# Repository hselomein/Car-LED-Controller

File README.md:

# Car-LED-Controller

Credits:
  - Corey Davis created the project and put together the prototypes.
  - Yves Avady wrote the code for this project.

This project controls an addressable LED Strip and LED matrix using the light inputs from a car electrical system.

With this project, we are taking an esp32 microcontroller and making an LED controller for the strip. 
The LED strip is a 12v WS2811 with 120 LEDs per meter

LED Strip Actions:
- Startup is a night rider style sweep 3 times until it is a solid white bar
- DRL Modes will control the LED strip brightness.

-  When DRLs are in Daytime Running Light Mode strip will be at full brightness
-  When DRLs are used as parking lights, the strip will be dimmed to a lower brightness
  
- Horn usage makes the lights turn dark amber to represent "Angry Mode"
- Indicators will show using a single chasing pattern that stays on for as long as the voltage is applied. This is to match the blink of the indicator circuit
- When hazard lights are on there will be a chasing pattern starting from the middle and ending at the ends
- There will be a button to cycle between Normal, Uber, and Lyft Modes
- Uber Mode, the led strip will be a Seafoam Greem color
- LYFT Mode, the led strip will be Magenta
There will be a physical switch installed to disable the light for law enforcement and/or vehicle inspection purposes

There are 5 voltage reading inputs 

  - DRL Left Sensing, 
  - DRL right Sensing,
  - Horn Sensing,
  - Left Indicator,
  - Right Indicator

At powerup LED strip will sweep 3 times each pass leaving the light on brighter until filled.
It'll stay filled white unless another mode is selected or an action happens

2 LED Matrices will be attached to the front and back of the vehicle and show 1 of 3 screens
  - Off or Blank for normal driving mode
  - Uber Mode: Shows Uber logo
  - Lyft Mode: Shows Lyft Logo

Actions:
DRL is in DRL Mode light will be at full brightness
DRL is in parking light mode and will be at half-brightness
When not in Uber or Lyft mode, the LED Matrix will be blank or off
Horn is pressed LED Strip will turn orange for the duration of the press
UBER Mode will turn the lights Cyan and the LED Matrix will show the Uber logo
Lyft Mide will turn the lights Magenta and the LED Matrix will show the Lyft Logo
Angry Mode will be some orangy red color, cant be RED as that is illegal in the front
The left indicator will show a chasing pattern, starting in the center and moving to the left side of the strip
The right indicator will show a chasing pattern, starting in the center and moving to the right side of the strip
Vehicle inspection mode, which will disable the lights, physical switch

There is a parts list so you can build this as well.

How to use with Platform-io IDE:
- You will need the Platformio-ide extension installed in VSCODE to compile the code
The src folder is where the code you want to compile and upload code to the ESP32
The main program code is in the file "main.cpp".

How to use with Arduino IDE
- The Arduino project files are located in the ArduinoIDE folder. This part is not complete still porting the code

This program is modular. You can enable or disable specific features by setting directives to true or false.

Build Configuration Options - This program is modular in the sense that you can have everything (LED Strip, LED Matrix) work or just cartain parts.  
See the Build Configuration Options to enable or disable certain features.

Examples:  
//Build Configuration Options  
  #define DEBUG false       //Enable serial output for debug, change to "false" to disable  
  #define SCREENTEST false  //To enable the boot up screen test, change to "true", to disable change to "false"  
  #define LED_MATRIX true   //Set to "true" if you want to use a 64x64 LED Matrix, "false" to disable  
  #define LED_STRIP true    //Set to "true" if you want to use the led strip, "false" to disable  
  #define NUM_MODES 2       //How many modes will the mode button handle (2 for Uber and Lyft signs)  

Code Notes:
- Car_LED_Controller-LED_Matrix_64x64.ino - this is the program for the 64x64 P2 LED Matrix for the Arduino ide, this still needs to be completed
- Part List - this is the shopping list of parts for this project

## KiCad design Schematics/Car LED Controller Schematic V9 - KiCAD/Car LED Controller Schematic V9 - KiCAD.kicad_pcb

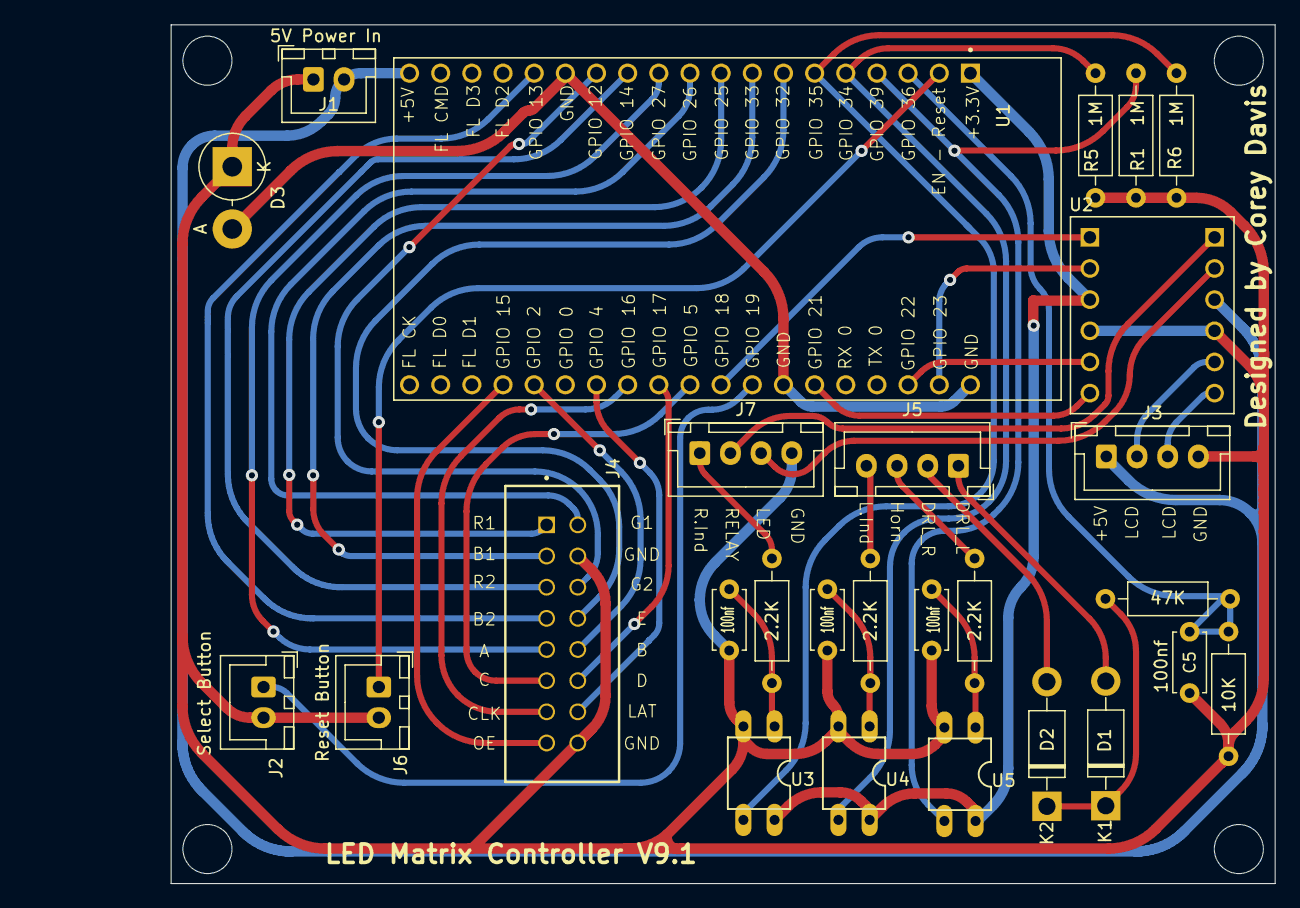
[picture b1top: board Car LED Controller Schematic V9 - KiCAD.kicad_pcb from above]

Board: 2 copper layers, 101.9 x 70.0 mm, 27 parts (0 on the bottom side), 41 nets.

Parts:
C1, C2, C3, C5: 100nf; C_Disc_D4.7mm_W2.5mm_P5.00mm
D1, D2: 1N4007; D_DO-41_SOD81_P10.16mm_Horizontal
D3: D_Schottky; D_DO-201AD_P5.08mm_Vertical_AnodeUp
J1: 5V Power In; JST_XH_B2B-XH-A_1x02_P2.50mm_Vertical
J2: Select Button; JST_XH_B2B-XH-A_1x02_P2.50mm_Vertical
J3: LCD Display; JST_XH_B4B-XH-A_1x04_P2.50mm_Vertical
J4: ZSS-108-01-F-D-506; SAMTEC_ZSS-108-01-F-D-506
J5: DRL, Horn, Indicator; JST_XH_B4B-XH-A_1x04_P2.50mm_Vertical
J6: Reset Button; JST_XH_B2B-XH-A_1x02_P2.50mm_Vertical
J7: DRL, Horn Sense; JST_XH_B4B-XH-A_1x04_P2.50mm_Vertical
R1, R5, R6: 1M; R_Axial_DIN0207_L6.3mm_D2.5mm_P10.16mm_Horizontal
R2, R3, R4: 2.2K; R_Axial_DIN0207_L6.3mm_D2.5mm_P10.16mm_Horizontal
R10: 47K; R_Axial_DIN0207_L6.3mm_D2.5mm_P10.16mm_Horizontal
R11: 10K; R_Axial_DIN0207_L6.3mm_D2.5mm_P10.16mm_Horizontal
U1: ESP32-DEVKITC-32D; MODULE_ESP32-DEVKITC-32D
U2: BOB-12009; CONV_BOB-12009
U3, U4, U5: PC817X3NSZ9F; DIL04

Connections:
+3.3V: U1.J2-1 (3V3), U2.LV, U3.4, U4.4, U5.4
+5V: J1.2, J3.1, U1.J2-19 (EXT_5V), U2.HV
/DRL Signal: C5.1, R10.1, R11.1, U1.J2-3 (SENSOR_VP)
/DRL_L: D1.2 (A), J5.1 (DRL_L)
/DRL_R: D2.2 (A), J5.2 (DRL_R)
/ESP32_GND: D3.2 (A), U1.J2-14 (GND1), U1.J3-1 (GND3), U1.J3-7 (GND2)
/Horn: J5.3 (Horn), R4.1
/Horn_Inp: R1.2, U1.J2-4 (SENSOR_VN), U5.3
/IND_L: J5.4 (IND_L), R3.1
/IND_R: J7.1 (IND_R), R2.1
/LCD_1: J3.2, U2.HV3
/LCD_2: J3.3, U2.HV4
/LED: J7.3 (LED), U2.HV2
/L_Ind_Inp: R5.2, U1.J2-5 (IO34), U4.3
/RELAY: J7.2 (Relay), U2.HV1
/R_Ind_Inp: R6.2, U1.J2-6 (IO35), U3.3
GND: C1.2, C2.2, C3.2, C5.2, D3.1 (K), J1.1, J2.2, J3.4, J4.04 (GND), J4.16 (GND), J6.2, J7.4 (GND), R1.1, R5.1, R6.1, R11.2, U2.GND_1 (GND), U2.GND_2 (GND), U3.2, U4.2, U5.2
unnamed: C1.1, R4.2, U5.1
unnamed: C2.1, R3.2, U4.1
unnamed: C3.1, R2.2, U3.1
unnamed: D1.1 (K), D2.1 (K), R10.2
unnamed: J2.1, U1.J3-8 (IO19)
unnamed: J4.09 (A), U1.J2-11 (IO27)
unnamed: J4.03 (B1), U1.J2-8 (IO33)
unnamed: J4.07 (B2), U1.J2-15 (IO13)
unnamed: J4.10 (B), U1.J3-15 (IO2)
unnamed: J4.11 (C), U1.J3-10 (IO5)
unnamed: J4.13 (CLK), U1.J3-12 (IO16)
unnamed: J4.12 (D), U1.J3-11 (IO17)
unnamed: J4.08 (E), U1.J2-7 (IO32)
unnamed: J4.02 (G1), U1.J2-10 (IO26)
unnamed: J4.06 (G2), U1.J2-13 (IO12)
unnamed: J4.14 (LAT), U1.J3-13 (IO4)
unnamed: J4.15 (OE), U1.J3-16 (IO15)
unnamed: J4.01 (R1), U1.J2-9 (IO25)
unnamed: J4.05 (R2), U1.J2-12 (IO14)
unnamed: J6.1, U1.J2-2 (EN)
unnamed: U1.J3-9 (IO18), U2.LV1
unnamed: U1.J3-6 (IO21), U2.LV4
unnamed: U1.J3-3 (IO22), U2.LV3
unnamed: U1.J3-2 (IO23), U2.LV2

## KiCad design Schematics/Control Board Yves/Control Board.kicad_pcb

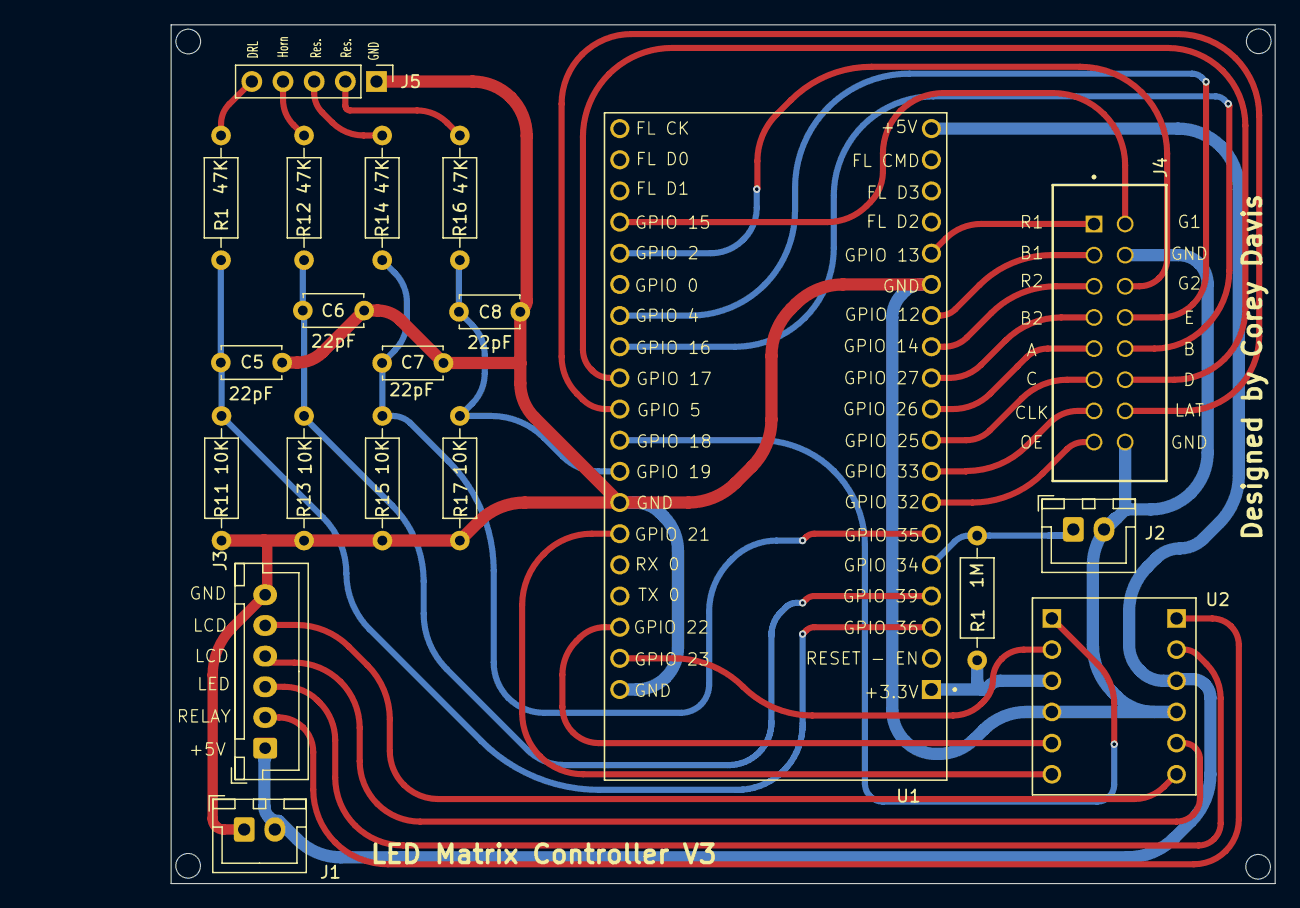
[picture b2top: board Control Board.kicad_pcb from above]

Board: 2 copper layers, 101.9 x 70.0 mm, 20 parts (0 on the bottom side), 34 nets.

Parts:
C5, C6, C7, C8: 22pF; C_Disc_D4.7mm_W2.5mm_P5.00mm
J1: 5V Power In; JST_XH_B2B-XH-A_1x02_P2.50mm_Vertical
J2: Select Button; JST_XH_B2B-XH-A_1x02_P2.50mm_Vertical
J3: LCD, Relay, LED Signal; JST_XH_B6B-XH-A_1x06_P2.50mm_Vertical
J4: ZSS-108-01-F-D-506; SAMTEC_ZSS-108-01-F-D-506
J5: Conn_01x05_Pin; PinHeader_1x05_P2.54mm_Vertical
R1: 1M; R_Axial_DIN0207_L6.3mm_D2.5mm_P10.16mm_Horizontal
R1#2, R12, R14, R16: 47K; R_Axial_DIN0207_L6.3mm_D2.5mm_P10.16mm_Horizontal
R11, R13, R15, R17: 10K; R_Axial_DIN0207_L6.3mm_D2.5mm_P10.16mm_Horizontal
U1: ESP32-DEVKITC-32D; MODULE_ESP32-DEVKITC-32D
U2: BOB-12009; CONV_BOB-12009

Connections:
+3.3V: R1.1, U1.J2-1 (3V3), U2.LV
+5V: J1.2, J3.1, U1.J2-19 (EXT_5V), U2.HV
GND: C5.2, C6.2, C7.2, C8.2, J1.1, J2.2, J3.6, J4.04 (GND), J4.16 (GND), J5.1, R11.2, R13.2, R15.2, R17.2, U1.J2-14 (GND1), U1.J3-1 (GND3), U1.J3-7 (GND2), U2.GND_1 (GND), U2.GND_2 (GND)
unnamed: J2.1, R1.2, U1.J2-5 (IO34)
unnamed: J3.2, U2.HV1
unnamed: J3.3, U2.HV2
unnamed: J3.4, U2.HV3
unnamed: J3.5, U2.HV4
unnamed: J4.09 (A), U1.J2-10 (IO26)
unnamed: J4.03 (B1), U1.J2-13 (IO12)
unnamed: J4.07 (B2), U1.J2-11 (IO27)
unnamed: J4.10 (B), U1.J3-12 (IO16)
unnamed: J4.11 (C), U1.J2-9 (IO25)
unnamed: J4.13 (CLK), U1.J2-8 (IO33)
unnamed: J4.12 (D), U1.J3-11 (IO17)
unnamed: J4.08 (E), U1.J3-13 (IO4)
unnamed: J4.02 (G1), U1.J3-16 (IO15)
unnamed: J4.06 (G2), U1.J3-15 (IO2)
unnamed: J4.14 (LAT), U1.J3-10 (IO5)
unnamed: J4.15 (OE), U1.J2-7 (IO32)
unnamed: J4.01 (R1), U1.J2-15 (IO13)
unnamed: J4.05 (R2), U1.J2-12 (IO14)
unnamed: J5.2, R16.2
unnamed: J5.3, R14.2
unnamed: J5.4, R12.2
unnamed: J5.5, R1#2.2
unnamed: U1.J3-9 (IO18), U2.LV1
unnamed: C8.1, R16.1, R17.1, U1.J3-8 (IO19)
unnamed: U1.J3-6 (IO21), U2.LV4
unnamed: U1.J3-3 (IO22), U2.LV3
unnamed: U1.J3-2 (IO23), U2.LV2
unnamed: C7.1, R14.1, R15.1, U1.J2-6 (IO35)
unnamed: C6.1, R12.1, R13.1, U1.J2-4 (SENSOR_VN)
unnamed: C5.1, R1#2.1, R11.1, U1.J2-3 (SENSOR_VP)

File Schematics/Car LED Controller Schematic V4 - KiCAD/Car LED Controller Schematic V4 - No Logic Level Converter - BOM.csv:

"Id","Designator","Footprint","Quantity","Designation","Supplier and ref",
1,"R16,R14,R12,R10","R_Axial_DIN0207_L6.3mm_D2.5mm_P10.16mm_Horizontal",4,"47K",,,
2,"J4","SAMTEC_TSS-108-01-L-D",1,"LED Matrix",,,
3,"J2","PinHeader_1x02_P2.54mm_Vertical",1,"Select Button",,,
4,"J1","PinHeader_1x02_P2.54mm_Vertical",1,"5V Power In",,,
5,"J3","PinHeader_1x06_P2.54mm_Vertical",1,"LCD, Relay, LED Signal",,,
6,"R11,R13,R17,R15","R_Axial_DIN0207_L6.3mm_D2.5mm_P10.16mm_Horizontal",4,"10K",,,
7,"J5","PinHeader_1x05_P2.00mm_Vertical",1,"DRL Horn Sense",,,
8,"U1","MODULE_ESP32-DEVKITC-32D",1,"ESP32-DEVKITC-32D",,,
9,"C7,C8,C5,C6","C_Disc_D4.7mm_W2.5mm_P5.00mm",4,"22pF",,,
10,"U2","CONV_BOB-12009",1,"BOB-12009",,,
11,"R1","R_Axial_DIN0207_L6.3mm_D2.5mm_P10.16mm_Horizontal",1,"1M",,,

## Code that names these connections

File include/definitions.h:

#ifndef _DEFINITIONS_H_
#define _DEFINITIONS_H_

//Build Configuration Options
  #define DEBUG false      //Enable serial output for debug, change to "false" to disable
  #define SCREENTEST false  //To enable the boot up screen test, change to "true", to disable change to "false"
  #define LED_MATRIX false   //Set to "true" if you want to use a 64x64 LED Matrix, "false" to disable
  #define LED_STRIP false   //Set to "true" if you want to use the led strip, "false" to disable
  #define LCD_DISPLAY true   //Set to "true" if you want to use the LCD Charcxv acter Display, "false" to disable
  #define NUM_MODES 2       //How many modes will the mode button handle (2 for Uber and Lyft signs)
  #define SHOW_VOLTAGES_LCD true //Set to "true" to display voltages on the LCD, "false" to disable

// Pins to device mapping
  #define RELAY_PIN_1 18                // Pin 18 => In1 Relay
  #define LED_PIN     23                // Pin 23 => LED Controller Signal
  #define DRL_PIN     ADC1_CHANNEL_0    // Pin 39 => DRL Sense

  #define MODE_PIN	  19  // Pin 19 +> Mode selection
  #define HORN_PIN    39  // Pin 39 => Horn Sense
  #define IND_L_PIN   34  // Pin 34 => Left Indicator 
  #define IND_R_PIN   35  // Pin 35 => Right Indicator 

  #define DEBOUNCE_TIME 100

  //Define lcd and led brightness
  #define MAX_BRIGHTNESS  255
  #define MIN_BRIGHTNESS  63
  #define MED_BRIGHTNESS  127

  #define RELAY_ON LOW
  #define RELAY_OFF HIGH

  #define NUM_SAMPLES     50              // number of analog samples to take per reading
  #define R1              47.0            // Resistor 1 value of voltage divider
  #define R2              10.0            // Resistor 2 value of voltage divider
  #define VOLT_DIV_FACTOR (R1+R2)/R2      //voltage divider factor
  #define RESISTOR_DIODE_OFFSET 0.3       //voltage drop across the diode
  #define GRND_OFFSET 0.8
  //static esp_adc_cal_characteristics_t ADC1_Characteristics;

  #define VOLT_BUF        1
  #define HI_VOLT         6
  #define LO_VOLT         2
  
//#ifndef
  //#define CONFIG_ESP_INT_WDT_TIMEOUT_MS 5000

#endif //_DEFINITIONS_H

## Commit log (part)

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2023-02-16 Fix mode change code
2023-02-17 formatting fixes
2023-02-17 lcd bug fixes
2023-02-17 fix autoscroll
2023-02-17 Remove Serial Print statements
2023-02-17 adding esp32 info
2023-02-17 Adding Fritzng Schematic parts for the hardware
2023-02-17 updating breadboard
2023-02-18 bb update
2023-02-19 Splitting code for ESP32 and Arduino UNO
2023-02-21 addmin new test code
2023-02-21 bug fixes and LCD test 1
2023-02-21 LCD test 2
2023-02-21 Test2
2023-02-21 fixed pins and comments
2023-02-21 fixed pin assign
2023-02-21 LDC test 3
2023-02-21 LCD test 4
2023-02-21 bug fix for strings
2023-02-21 suntax bug fix
2023-02-21 add delay
2023-02-21 print bug fix
2023-02-21 remove lcd
2023-02-21 brightness fix
2023-02-21 improve voltage calculations
2023-02-21 fix voltage calculation
2023-02-21 fix comments
2023-02-21 fix 0 voltage bug
2023-02-21 Adding Uptime for LCD Screen using new LCD library
2023-02-23 adding test done days and ago no intention to keep
2023-02-23 Making it actually work with the correct HW setup
2023-02-23 Found out that pin 12 is a bootsrapping pin
2023-02-23 adding new LCD data
2023-02-23 fixed aref, commentour lcd in loop
2023-02-23 adding colorpallet
2023-02-23 moving examples to the examples folder
2023-02-24 add HD44789 test program
2023-02-24 Update to new led library
2023-02-24 fix color values
2023-02-24 fix declarations and formatting
2023-02-24 Fix color bug in startup sequence
2023-02-24 fix voltage
2023-02-24 led parameter tuning
2023-02-24 adjust voltage parameters
2023-02-24 remove not needed constants
2023-02-24 tune voltage and color
2023-02-24 adjust vals
2023-02-24 fix oob bug
2023-02-24 tune voltage values
2023-02-24 remove notes
2023-02-24 tuned voltage values
2023-02-24 Create Tools.txt
    Useful tools needed for development and troubleshooting
2023-02-25 Less green equals more orange
2023-02-26 Added LCD and its working with some flicker
2023-02-26 playing with removing lcd clear
2023-02-26 playing around with delay timings
2023-02-26 singular funtion to read battery, need help
2023-02-27 adding values to make it work with my esp32
2023-02-27 update adc example
2023-02-27 fixing resistor values
2023-02-27 fix print
2023-02-27 Implement ACD Calibration
2023-02-27 Fix ADC readings
2023-02-27 minor fixes
2023-02-27 Set LCD to core 1
2023-02-27 Update LCD text orientation
2023-02-27 Fix bugs
2023-02-27 Fix LCD display bug
2023-02-27 LCD format adjustment
2023-02-27 fixed lcd formatting and variable display
2023-02-27 Update LCD display
2023-02-27 Minor bug fixes
2023-02-27 change delay
2023-02-27 minor tuning
2023-02-27 adding hall sensor notes
2023-02-27 Preparing for Release v0.1
2023-03-04 editing for clarity
2023-03-05 Test code works with hardware.
2023-03-05 Working, added library reference
2023-03-05 formatting cleanup, working test code
2023-03-05 Intrgrated Lyft, Uber Mode
2023-03-05 Integrated Lyft-Uber Mode
2023-03-05 revert cause i changed wrong file
2023-03-07 Fixed LCD Display, All code works!, Ready for car
2023-03-07 Update code structure
2023-03-07 added global
2023-03-07 fixed comment
2023-03-07 Fix ; bug
2023-03-08 Bug Fix
2023-03-08 migrate to object from enum
2023-03-08 looop move
2023-03-08 Use button count
2023-03-08 startup bug fix
2023-03-08 add init function
2023-03-08 change led step to 2
2023-03-08 add 2nd led
2023-03-08 change led wave logic
2023-03-08 fix start sequence bug
2023-03-08 fix bug
2023-03-08 remove delay
2023-03-08 add show
2023-03-09 Create Parts List
2023-03-10 adding more notes
2023-03-10 Updating breadboard to match prototype
2023-03-10 Update Parts List
2023-03-17 updated schematic
2023-05-04 Create Emblem-Lyft.c
    Added Lyft Image array
2023-05-05 adding led matrix committed
2023-05-05 folder reorg
2023-05-05 adding led martix code
2023-05-05 adding bitmap icons
2023-05-06 Test
2023-05-06 Test lib
2023-05-06 fixed semicolon
2023-05-06 test lyft logo
2023-05-06 fix color
2023-05-06 fix color mapping
2023-05-06 center image
2023-05-06 set white background
2023-05-06 added logo
2023-05-06 fixing logos
2023-05-06 new logo
2023-05-06 fix offset
2023-05-06 fix size
2023-05-06 reduce memory
2023-05-06 UBER logo
2023-05-06 fix logo
2023-05-06 fix lyft
2023-05-06 cleanup
2023-05-06 updating...
2023-05-08 Add files via upload
    Help you figure out what pins to use
2023-05-09 new example
2023-05-09 aste
2023-05-09 reorg
2023-05-10 New Logos
2023-05-10 for arduino ide
2023-05-10 fixes
2023-05-10 syning arduino ide
2023-05-10 syncging arduino
2023-05-10 consolidating duplicate code
2023-05-10 fixed refresh
2023-05-10 color fix
2023-05-10 set brightness
2023-05-10 test timer
2023-05-10 update test matrix
2023-05-12 added dim variables
2023-05-12 Brightness Adjust
2023-05-14 Project Reorganization to platformio
2023-05-15 adding pxmatrix test to main for testing
2023-05-15 added platformio ide instructions
2023-05-15 adding more data
2023-05-15 spreadsheet
2023-05-15 added ESP32 38 pinout
2023-05-16 adding pinouts to spreadsheet
2023-05-17 adding platformio compatible code
2023-05-17 platformio
2023-05-18 led matrix port into main code
2023-05-18 Added fully working code
2023-05-18 adding working code
2023-05-19 cleaup
2023-05-19 set up configuration options
2023-05-19 housekeeping
2023-05-19 name consistency
2023-05-20 fixed serial monitor speed
2023-05-20 removed deleted file info
2023-05-20 preparing code for arduinoide
2023-05-23 Create PCB Library
2023-07-03 Restructuring 1
2023-07-03 fix 2
2023-07-03 fix 3
2023-07-03 fix again
2023-07-03 another fix
2023-07-23 adding kicad schematic, pcb, and libraries
2023-07-23 fixing declarations
2023-07-25 Yves Schematic
2023-07-25 cleanup of pcb
2023-07-25 pcb revisions
2023-07-28 more pcb designs
2023-07-29 adding libraries to pcb
2023-08-03 more pcb
2023-08-04 schematic with logic level converter
2023-08-21 adding esp32
2023-08-21 updating pcbs
2023-08-21 added pcb
2023-08-21 adding models
2023-08-21 added second connector
2023-08-21 added more details
2023-08-22 adding more models
2023-08-22 added resistor model
2023-08-22 added all remeining models
2023-08-22 made some things
2023-08-28 update schmetic and pcb
2023-08-29 fixed led matrix pinout
2023-08-29 modle update
2023-08-29 Plastic Shell Mockup
2023-09-01 added alternate pinouts for lcd matrix
2023-09-01 fixed DRC issues
2023-09-03 pcb update
2023-09-04 adjusting final led strip size to 161
2023-09-09 update number of samples to 50
2023-09-09 platformio upgrade
2023-09-18 install on mew machine
2023-09-18 syncing machines
2023-10-11 added led pixel calculations, and rgb, rgbw define
2023-10-11 added led pixeld calclualtions, rgb, rgbw define
2023-10-11 adding 2 additional inputs as comments
2023-10-16 Temporary fix for car behaviors
2023-10-16 Documenting Car Behaviors
2023-10-16 Adding car electrical docs
2023-10-17 adding additional Drl input and indicator function
2023-10-17 adding second drl and indicator functions
2023-10-20 Added indicator and fixed drl variables
2023-10-26 whole lotta fun
2023-10-26 Additional ADC inputs added, Start debuging ADC
2023-10-27 Added indicator debug options
2023-10-27 check removing directives
2023-10-27 Fix typo
2023-10-27 Check if without braces
2023-10-27 Remove all unneeded curly braces
2023-10-27 remove directives
2023-10-27 Rearrange declarations and add a header file
2023-10-27 remove code from header files
2023-10-27 Add includes
2023-10-27 add globals
2023-10-27 fix case sensitive stuff
2023-10-27 convert defines to floats
2023-11-11 this does compile, did not test yet
2023-11-26 Adding more CAD and 3D Models
2023-11-28 PCB and Schematic updates
2023-11-28 Adding SimpleButton Library
2023-11-28 Updateing PCB and Schemtic
2023-11-28 update properties
2023-12-05 horn optocoupler button working
2023-12-06 Everything Works As Advertised!
2023-12-06 added hazard warning to lcd
2023-12-07 updating the readme
2023-12-07 Added the ability to remove the led matrix
2023-12-07 fixing formatting
2023-12-08 Create TaskLCD_V9.h
    Adding TaskLDC header file for V9 PCB
2023-12-09 Creating TaskLCD for V9 Boards
2023-12-11 update indicator and hazard functions
2023-12-11 added startup drl states
2023-12-11 LCD Text formatting changes
2023-12-13 added button inturrups for testing new feature
2023-12-13 update drl levels for lcd
2023-12-15 Fixed DRL monitor function (drl_mon())
2023-12-15 hazard timing and spacing fixed
2024-02-20 slimming code and working on hazard function
2024-02-23 updating
2024-03-02 Update to schematic and PCBupdate
2024-03-02 working code, still need to work on ind timings
2024-03-02 updated pcb and schematic
2024-03-04 PCB upload to manufacturing
2024-03-04 adding deprecated libracy for legacy code
2024-03-07 pcb updates
2024-03-07 weird issue
2024-03-07 Working Code, everything works as expected
2024-03-07 Removed BTN_INTERRUPT code, unsed and buggy
2024-03-07 Moved Brightness, relay, and LED Martix actions to DRL_MON function - Working
2024-03-07 removed BTN_INTERRUPTS related code - working
2024-03-07 removed extra LED Martix Pinouts - working
2024-03-07 create button_function handle mode and indicator buttons
2024-03-08 Removed addition PCB Bdard Types and code cleanup
2024-03-08 correcting color values for white
2024-03-08 whitespace cleanup
2024-03-09 Added the ability to disable the led strip and led matrix
2024-03-09 added build configuration options to readme
2024-03-18 created definitions.h file
2024-03-18 changed delay() to non blocking delay
2024-03-18 moved definitions to definition.h
2024-03-18 definitions.h related cleanup
2024-03-18 undefined reference to 'initTaskLCD'
2024-03-18 VS cleanup
2024-03-18 Remove non blocking delay from ind and hazard functions
2024-04-12 Cad edits
2024-04-12 uploading
2024-04-12 Cad Fixes
2024-07-07 updates to model
2024-07-07 updating TaskLCD V9 issues
2024-07-08 added locking variables to indicator and hazard functions
2024-07-08 idf update
2024-07-23 schematic updates
2024-07-23 Added new dispaly option for LCD
2024-07-23 fixed indicator funtions and detection
2024-07-25 removed GRND_OFFSET from end of equation
2024-07-25 changed samples to 750
2024-07-25 splittin TaskLDC_V9 to h and cpp files
2024-07-25 Restructuring part 0.0001
2024-07-25 led variable fix
2024-07-25 fix TaskLCD
2024-07-26 Changing build type to release mode
2024-07-26 IDF updates
2024-07-26 going back to orginal samples of 50
2024-07-26 converted deprecated ADC attenuation to something supported
2024-07-26 dont want to merge main code to release branch
2024-07-26 ide updates
2024-07-26 TaskLCD to class conversion
2024-07-26 Major Restructure
2024-07-26 minor fix
2024-07-26 rename files
2024-07-28 Set SHOW_VOLTAGES_LCD to false and NUM_SAMPLES to 100
2024-07-28 platformio updates
2024-10-04 adding linbus reading developemt
2024-10-07 Bug fixes
2024-10-07 start using bit operations
2024-10-07 Change to working with a string that is a binary representation
2024-10-07 fixed break and sync and id
2024-10-07 fix break frame
2024-10-07 syntax error
2024-10-07 restructure
2024-10-31 gerenic fixes
2024-10-31 log file additions
2024-10-31 serial log ftom release 1.1
2024-10-31 Updated Libraries
